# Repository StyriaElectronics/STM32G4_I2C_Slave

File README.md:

# 🧪 STM32G431 – I²C Slave ADC Sampler with Trigger & Calibration

This project demonstrates how to configure an **STM32G431** as an **I²C slave** that samples **two ADC channels** at **10 kHz for 1 second** (10,000 samples per channel). The result is transmitted to a master (e.g., Raspberry Pi) over I²C. Sampling can be triggered either by I²C command or via **GPIO trigger input on PA8**.

## 📂 Project Structure

```
├── Core/                → STM32 application source
├── Drivers/             → STM32 HAL and CMSIS
├── Hardware/            → KiCad PCB design files
├── Python3_Script/      → Raspberry Pi script to trigger and read
├── docs/                → Documentation and visuals
├── .gitignore           → Git exclusions
├── I2C_ADC.ioc          → CubeMX configuration file
├── LICENSE              → CC0 license
└── README.md            → This file
```

## ✨ Features

- 🔌 **I²C Slave Interface**
- 📈 **Dual 10 kHz ADC Sampling**
- ⏱ **Timer-based precision using TIM6**
- 🔦 **Status LED controlled via I²C**
- 🧮 **CRC8 for data integrity**
- 🐍 **Python script for Raspberry Pi**
- 🛠️ **KiCad hardware project included**

## 🔄 I²C Protocol

| Command | Description                             |
|---------|-----------------------------------------|
| `0x00`  | Turn LED **ON**                         |
| `0x01`  | Turn LED **OFF**                        |
| `0x02`  | Start ADC buffer transmission (20001 B) |
| `0x03`  | Start 1 s sampling                      |
| `0x04`  | Start calibration (ADC1 blink)          |
| `0x05`  | Save offset of ADC1                     |
| `0x06`  | Start calibration (ADC2 blink)          |
| `0x07`  | Save offset of ADC2                     |

## 🛠 Hardware

The `Hardware/` folder contains the KiCad files for the PCB design:

- Schematic (`.kicad_sch`)
- Layout (`.kicad_pcb`)
- Gerber files
- BOM (Bill of Materials)

These files allow you to fabricate or modify the board as needed.

## 🐍 Python Example (Raspberry Pi)

A script using `smbus2` to trigger and read the data from the STM32:

```bash
cd Python3_Script/
python3 read_adc_data.py
```

Output will display the values of both ADC channels and CRC validation.

## 📄 License

This project is licensed under **CC0 1.0 Universal (Public Domain Dedication)**. You can use it freely without attribution – though a ⭐ on GitHub is always appreciated :)

⚠️ **Disclaimer**:  
This project is provided "as is" without warranty of any kind, either expressed or implied.  
In no event shall the author(s) be liable for any claim, damages, or other liability arising from, out of, or in connection with the use or other dealings in this project.

## 🙌 Contributing

Feel free to fork the repository, open issues, or submit pull requests.  
PRs improving timing, robustness or adding DMA support are welcome!

## ⭐️ If You Like It...

...consider giving this repo a ⭐️ to support the project!

Made with ❤️ by **Styria Electronics**  
🌐 [styria-electronics.at](https://styria-electronics.at)

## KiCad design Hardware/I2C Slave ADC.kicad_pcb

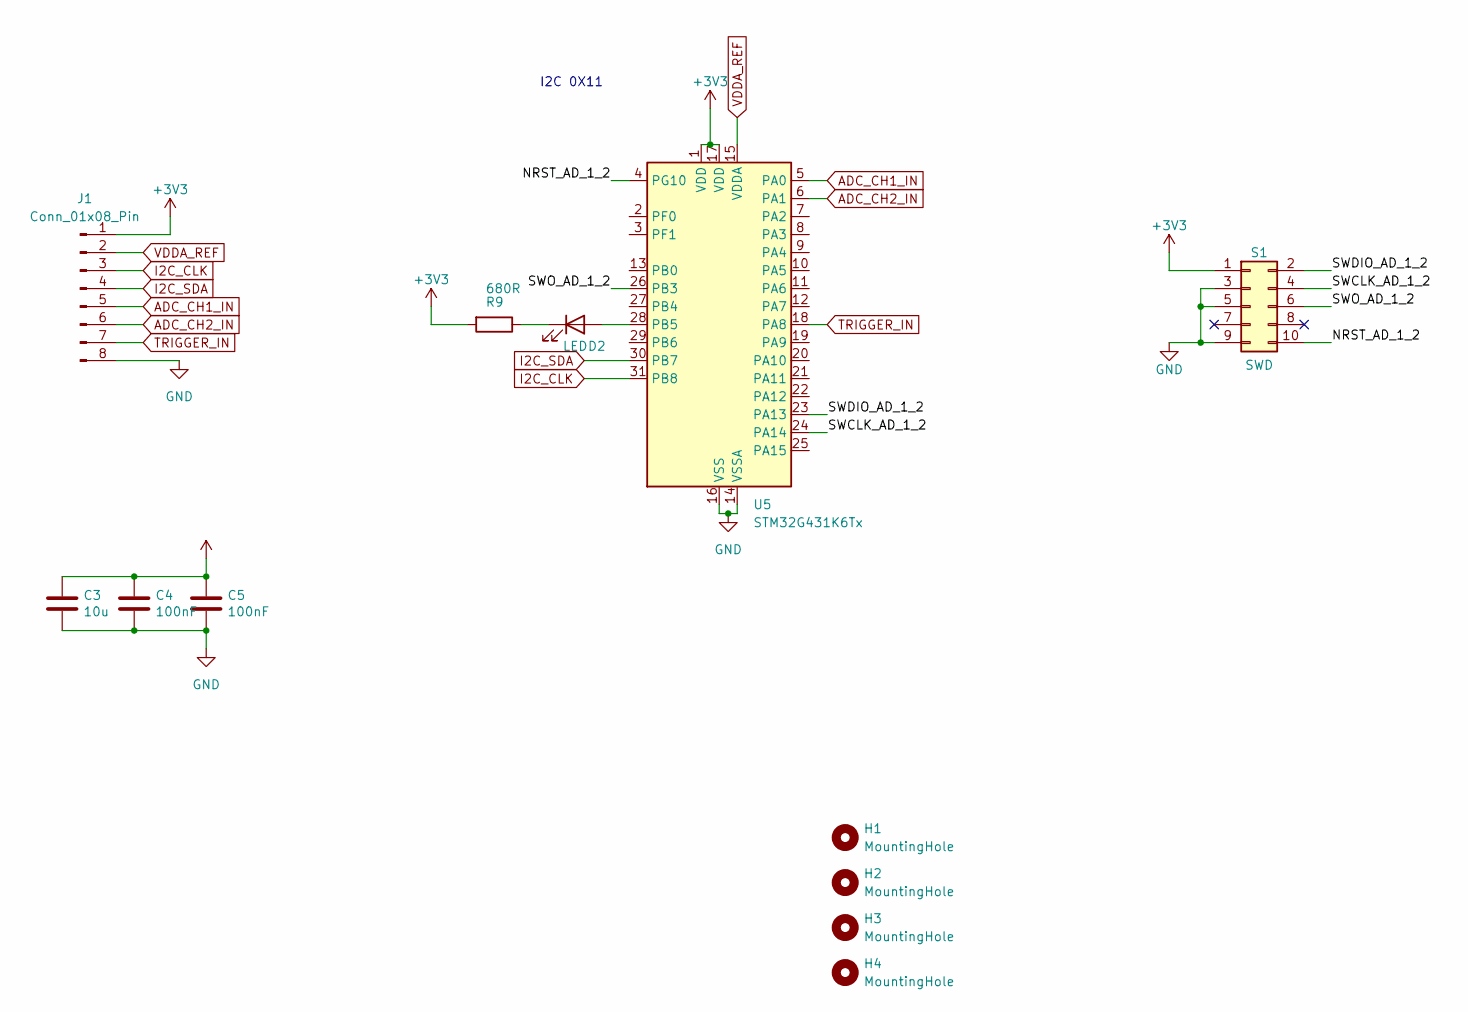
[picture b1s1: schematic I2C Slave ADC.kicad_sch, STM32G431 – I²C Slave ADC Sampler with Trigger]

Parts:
C3: 10u; C_0805_2012Metric; Part Description 10uF 10% 10V Ceramic Capacitor X7R 0805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
C4, C5: 100nF; C_0805_2012Metric; Part Description 10uF 10% 10V Ceramic Capacitor X7R 0805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
D2: LED; LED_0805_2012Metric
H1, H2, H3, H4: MountingHole; MountingHole_3.2mm_M3_ISO14580
J1: Conn_01x08_Pin; PinSocket_1x08_P2.54mm_Vertical
R9: 680R; R_0603_1608Metric; Part Description Resistor 10R M1005 1% 63mW
S1: SWD; PinHeader_2x05_P1.27mm_Vertical_SMD
U5: STM32G431K6Tx; LQFP-32_7x7mm_P0.8mm

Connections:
+3V3: C3.1, C4.1, C5.1, J1.1, R9.2, S1.1, U5.1 (VDD), U5.17 (VDD)
/NRST_AD_1_2: S1.10, U5.4 (PG10)
/SWCLK_AD_1_2: S1.4, U5.24 (PA14)
/SWDIO_AD_1_2: S1.2, U5.23 (PA13)
/SWO_AD_1_2: S1.6, U5.26 (PB3)
ADC_CH1_IN: J1.5, U5.5 (PA0)
ADC_CH2_IN: J1.6, U5.6 (PA1)
GND: C3.2, C4.2, C5.2, J1.8, S1.3, S1.5, S1.9, U5.14 (VSSA), U5.16 (VSS), U5.32 (VSS)
I2C_CLK: J1.3, U5.31 (PB8)
I2C_SDA: J1.4, U5.30 (PB7)
unnamed: D2.2 (A), U5.28 (PB5)
unnamed: D2.1 (K), R9.1
TRIGGER_IN: J1.7, U5.18 (PA8)
VDDA_REF: J1.2, U5.15 (VDDA)

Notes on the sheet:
I2C 0X11

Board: 2 copper layers, 12 parts (0 on the bottom side), 14 nets, no tracks yet.

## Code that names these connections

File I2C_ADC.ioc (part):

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Mcu.Name=STM32G431K(6-8-B)Tx
Mcu.Package=LQFP32
Mcu.UserName=STM32G431K6Tx
PA0.Mode=IN1-Single-Ended
PA0.Signal=ADC1_IN1
PA1.Mode=IN2-Single-Ended
PA1.Signal=ADC2_IN2
PA8.GPIOParameters=GPIO_Label
PA8.GPIO_Label=TRIGER
PA8.Signal=GPIO_Input
PB5.GPIOParameters=GPIO_Label
PB5.GPIO_Label=LED
PB5.Signal=GPIO_Output
PB7.Mode=I2C
PB7.Signal=I2C1_SDA
PB8-BOOT0.Mode=I2C
PB8-BOOT0.Signal=I2C1_SCL
RCC.HSE_VALUE=8000000
RCC.SYSCLKFreq_VALUE=170000000
RCC.SYSCLKSource=RCC_SYSCLKSOURCE_PLLCLK
board=custom

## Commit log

2025-04-09 Add Readme
2025-04-09 Add I2C
2025-04-10 Add ADC
2025-04-10 Add Python3 script
2025-04-10 Change Readme.me
2025-04-10 🔧 Fix .gitignore: include STM32CubeIDE project files
2025-04-10 📦 Add missing project files for STM32CubeIDE
2025-04-13 ADD Calibrations funktion
2025-04-13 Edit README
2025-04-13 ADD KICad Files
2025-04-13 Apply updated .gitignore and clean up tracked files
2025-04-13 Apply updated

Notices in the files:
README.md:
License: CC0-1.0
